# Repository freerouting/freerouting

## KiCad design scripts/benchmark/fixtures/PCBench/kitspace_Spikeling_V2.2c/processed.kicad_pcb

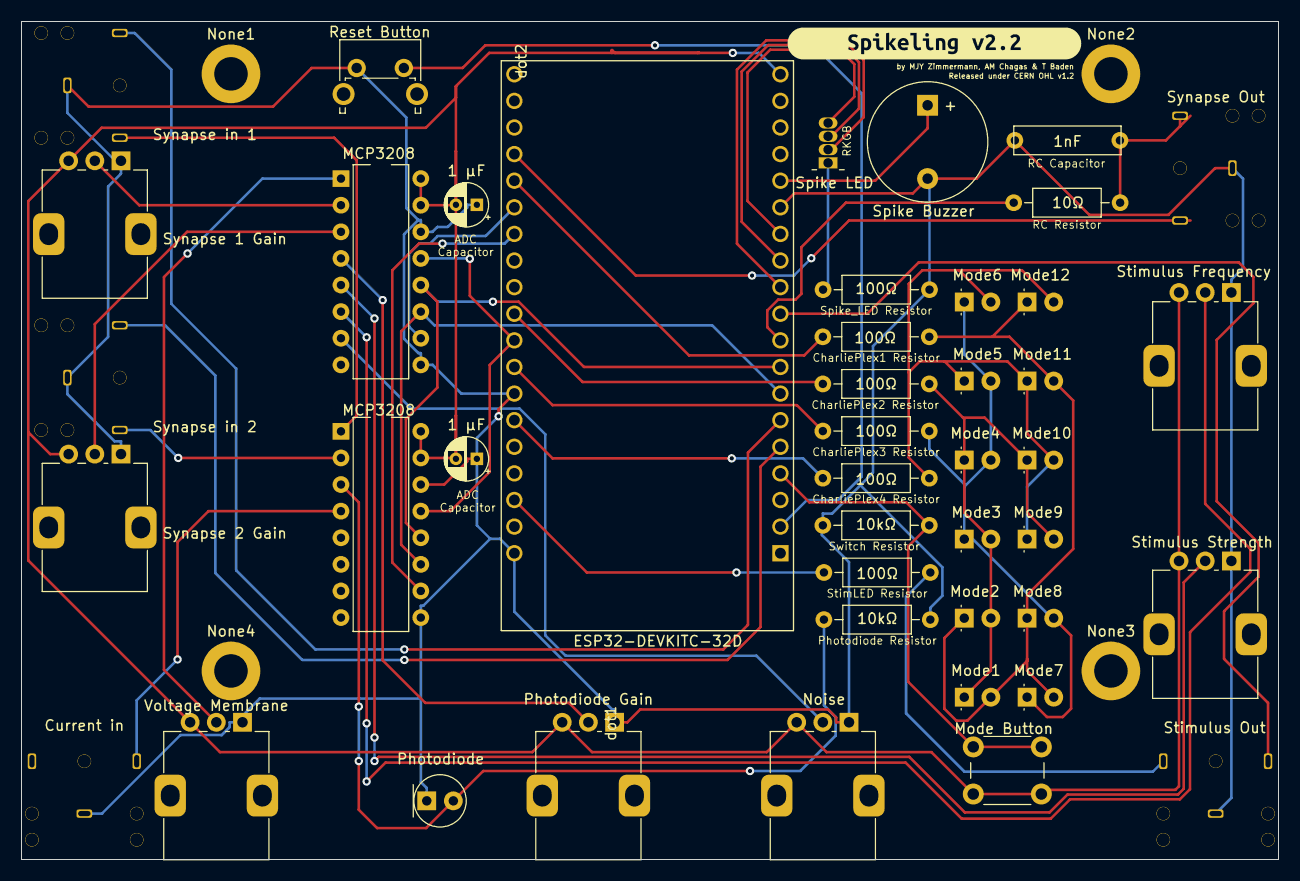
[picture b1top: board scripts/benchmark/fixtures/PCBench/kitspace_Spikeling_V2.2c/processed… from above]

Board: 2 copper layers, 120.0 x 80.0 mm, 51 parts (0 on the bottom side), 41 nets.

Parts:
BZ1: Spike Buzzer; Buzzer_11.5x9.5RM5
C1, C2: 1 μF; CP_Radial_D4.0mm_P2.00mm
C3: 1nF; C_Disc_D10.0mm_W2.5mm_P5.00mm
D1: Photodiode; LED_D5.0mm
D2: Mode1; LED_D3.0mm
D3: Mode2; LED_D3.0mm
D4: Mode3; LED_D3.0mm
D5: Mode4; LED_D3.0mm
D6: Mode5; LED_D3.0mm
D7: Mode6; LED_D3.0mm
D8: Mode7; LED_D3.0mm
D9: Mode8; LED_D3.0mm
D10: Mode9; LED_D3.0mm
D11: Mode10; LED_D3.0mm
D12: Mode11; LED_D3.0mm
D13: Mode12; LED_D3.0mm
D14: Spike LED; LED_D5.0mm-4_RGB
J1: Synapse Out; Spikeling Audio Jack 3.5mm
J2: Synapse in 1; Spikeling Audio Jack 3.5mm
J4: Current in; Spikeling Audio Jack 3.5mm
J5: Stimulus Out; Spikeling Audio Jack 3.5mm
None1, None3, None4: MountingHole_3.2mm_M3_DIN965_Pad
None2: MountingHole_M3; MountingHole_3.2mm_M3_DIN965_Pad
R1: 10Ω; R_Axial_DIN0207_L6.3mm_D2.5mm_P10.16mm_Horizontal
R2, R5: 10kΩ; R_Axial_DIN0207_L6.3mm_D2.5mm_P10.16mm_Horizontal
R3, R4, R6, R7, R8, R9: 100Ω; R_Axial_DIN0207_L6.3mm_D2.5mm_P10.16mm_Horizontal
RV1: Synapse 1 Gain; Spikeling Potentiometer
RV2: Synapse 2 Gain; Spikeling Potentiometer
RV3: Voltage Membrane; Spikeling Potentiometer
RV4: Noise; Spikeling Potentiometer
RV5: Photodiode Gain; Spikeling Potentiometer
RV6: Stimulus Strength; Spikeling Potentiometer
RV7: Stimulus Frequency; Spikeling Potentiometer
SW1: Mode Button; SW_PUSH_6mm_H13mm
SW2: Reset Button; Spikeling reset button
U1: ESP32-DEVKITC-32D; MODULE_ESP32-DEVKITC-32D
U2, U3: MCP3208; DIP-16_W7.62mm
dot1: Spikeling_neuron; Spikeling_Photoreceptor
dot2: Spikeling_neuron; Spikeling_Neuron
e: Synapse in 2; Spikeling Audio Jack 3.5mm
kibuzzard-633362FE: G***; kibuzzard-633362FE

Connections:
/00: U1.33, U2.10
/02: R6.1, U1.34
/04: U1.32, U3.10
/05: R7.1, U1.29
/12: D14.4, U1.13
/13: BZ1.1, U1.15
/14: D14.3, U1.12
/15: J1.T, U1.35
/18: U1.28, U2.13, U3.13
/19: R8.1, U1.27
/21: R9.1, U1.25
/22: R3.1, U1.22
/25: R1.1, U1.9
/26: J5.R, U1.10
/27: D14.1, U1.11
/32: U1.7, U2.11, U3.11
/33: U1.8, U2.12, U3.12
/34: U1.5, e.T
/35: J2.T, U1.6
/39: R5.1, SW1.1, U1.4
/100: RV3.2, U2.1
/101: RV1.2, U2.2
/102: RV2.2, U2.3
/103: RV5.2, U2.4
/104: RV6.2, U2.5
/105: RV7.2, U2.6
/106: RV4.2, U2.7
/200: J2.R, U3.1
/201: U3.2, e.R
/202: D1.2, R2.1, U3.3
/203: J4.R, U3.4
GNDREF: BZ1.2, C1.1, C2.1, C3.2, D1.1, J1.S, J2.S, J4.S, J5.S, R2.2, R4.1, R5.2, RV1.1, RV2.1, RV3.1, RV4.1, RV5.1, RV6.1, RV7.1, SW2.1, U1.14, U1.20, U1.26, U2.9, U2.14, U3.9, U3.14, e.S
unnamed: C3.1, J1.R, R1.2
unnamed: J5.T, R3.2
unnamed: D14.2, R4.2
unnamed: D2.2, D3.1, D8.2, D9.1, D12.2, D13.1, R6.2
unnamed: D2.1, D3.2, D4.2, D5.1, D10.2, D11.1, R7.2
unnamed: D4.1, D5.2, D6.2, D7.1, D8.1, D9.2, R8.2
unnamed: D6.1, D7.2, D10.1, D11.2, D12.1, D13.2, R9.2
unnamed: SW2.2, U1.2
VCC: C1.2, C2.2, RV1.3, RV2.3, RV3.3, RV4.3, RV5.3, RV6.3, RV7.3, SW1.2, U1.19, U2.15, U2.16, U3.15, U3.16

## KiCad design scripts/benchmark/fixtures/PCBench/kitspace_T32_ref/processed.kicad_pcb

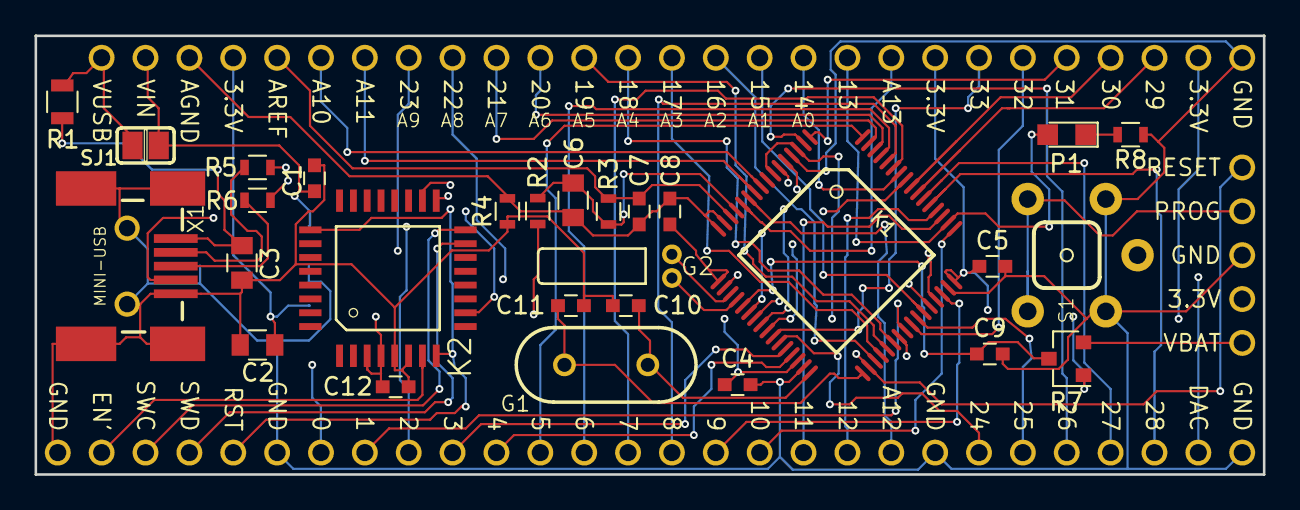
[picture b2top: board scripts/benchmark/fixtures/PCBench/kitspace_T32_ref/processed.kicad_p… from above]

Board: 4 copper layers, 71.1 x 25.4 mm, 89 parts (1 on the bottom side), 66 nets.

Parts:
C1, C4, C5, C7, C8, C9, C12: 0.1uF; C_0603
C2, C3, C6: 2.2uF; C_0805
C10, C11: 22pF; C_0603
G1: 16MHz; HC49US
G2: 32.768kHz; TC26H
K1: MK20DX256VLH7; LQFP64-05
K2: MKL04Z32VLC4; LQFP32-08
P1: LED_0805
R1: FUSE; R_0805
R2, R4: R_0603
R3, R8: 470R; R_0603
R5, R6: 33R; R_0603
R7: SOT-23
S1: ALPS_SKHH
SJ1: SOLDERJUMPER
SX1, SX2, SX3, SX4, SX5, SX6, SX7, SX8, SX9, SX10, SX11, SX12, SX13, SX14, SX15, SX16, SX17, SX18, SX19, SX20, SX21, SX22, SX23, SX24, SX25, SX26, SX27, SX28, SX29, SX30, SX31, SX32, SX33, SX34, SX35, SX36, SX37, SX38, SX39, SX40, SX41, SX42, SX43, SX44, SX45, SX46, SX47, SX48, SX49, SX50, SX51, SX52, SX53, SX54, SX55, SX56, SX57, SX58, SX59, SX60: PIN; PTH_39MIL
T1: MCP1825S; SOT-223
X1: MINI-USB; MOLEX_SD-67503-010

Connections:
/N$1: K2.7, SX59.1
/N$2: K1.22, K2.16, SX58.1
/N$3: K1.24, K2.17
/N$5: C10.1, G1.1, K1.32
/N$6: C11.1, G1.2, K1.33
/N$7: G2.2, K1.19
/N$8: G2.1, K1.20
/N$9: K2.18, S1.1, S1.2, SX40.1
/N$10: K1.5, R6.2
/N$11: C8.1, K1.17
/N$12: K1.34, K2.8, K2.25, SX38.1, SX56.1
/N$13: C7.1, K1.14, R3.2, SX16.1
/N$14: K1.6, R5.2
/N$15: C6.1, K1.13, R2.1, R3.1
/N$16: R6.1, X1.3
/N$17: R5.1, X1.2
/N$18: C3.1, R1.1, X1.1
/N$19: K1.23, K2.10, X1.4
/N$21: K1.45, SX5.1
/N$22: K1.44, SX6.1
/N$23: K1.63, SX7.1
/N$24: K1.62, SX8.1
/N$25: K1.37, SX9.1
/N$26: K1.38, SX10.1
/N$27: K1.36, SX11.1
/N$28: K1.35, SX13.1
/N$29: K1.43, SX15.1
/N$30: K1.58, SX17.1
/N$31: K1.50, P1.2, SX18.1
/N$32: K1.52, SX19.1
/N$33: K1.51, SX20.1
/N$34: K1.49, SX21.1
/N$35: K1.46, SX22.1
/N$36: K1.60, SX23.1
/N$37: K1.59, SX24.1
/N$38: K1.61, SX25.1
/N$39: K1.64, SX26.1
/N$40: K1.29, SX27.1
/N$41: K1.28, SX28.1
/N$42: K1.57, SX29.1
/N$43: K1.40, SX30.1
/N$44: K1.39, SX31.1
/N$45: K1.12, SX33.1
/N$46: K1.26, SX35.1
/N$47: K1.41, SX36.1
/N$48: K1.1, SX37.1
/N$49: K1.56, SX39.1
/N$50: K1.55, SX41.1
/N$51: K1.53, SX43.1
/N$52: P1.1, R8.2
/N$53: C6.2, C7.2, C8.2, K1.15, K1.16, R4.2, SX3.1
/N$54: K1.18, SX52.1
/N$55: K1.11, SX51.1
/N$57: K1.27, SX49.1
/N$58: K1.42, SX48.1
/N$59: K1.2, SX47.1
/N$60: K1.54, SX45.1
/N$61: C1.1, SJ1.2, SX2.1, T1.1
/N$63: R7.2, SX46.1
/N$64: K1.10, SX12.1
/N$65: K1.9, SX14.1
/N$67: R1.2, SJ1.1, SX1.1
/N$68: C9.1, K1.21, R7.3
/N$69: C2.1, C4.1, C5.1, C12.1, K1.3, K1.7, K1.30, K1.48, K2.3, K2.4, R2.2, R7.1, SX4.1, SX34.1, SX44.1, SX54.1, T1.3
/N$70: K1.25, K2.15, SX57.1
GND: C1.2, C2.2, C3.2, C4.2, C5.2, C9.2, C10.2, C11.2, C12.2, K1.4, K1.31, K1.47, K2.5, K2.6, R4.1, R8.1, S1.3, S1.4, SX32.1, SX42.1, SX50.1, SX53.1, SX55.1, SX60.1, T1.2, T1.4, X1.5, X1.P$1, X1.P$2, X1.P$3, X1.P$4, X1.P$5, X1.P$6

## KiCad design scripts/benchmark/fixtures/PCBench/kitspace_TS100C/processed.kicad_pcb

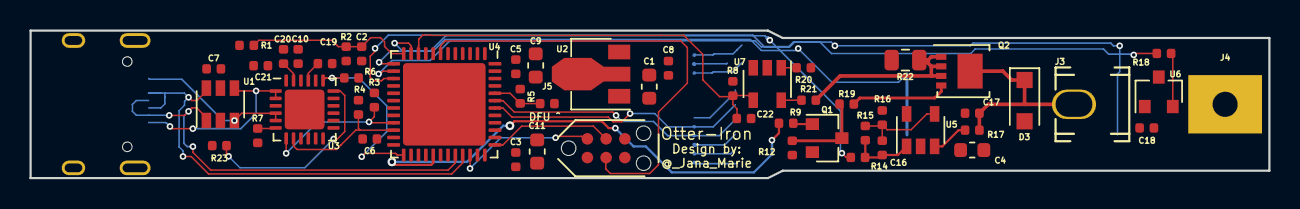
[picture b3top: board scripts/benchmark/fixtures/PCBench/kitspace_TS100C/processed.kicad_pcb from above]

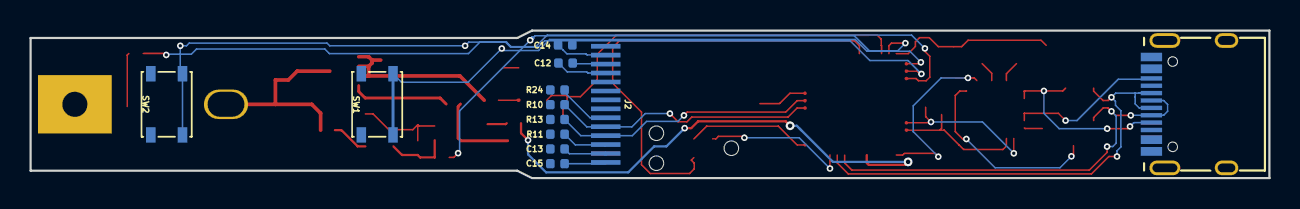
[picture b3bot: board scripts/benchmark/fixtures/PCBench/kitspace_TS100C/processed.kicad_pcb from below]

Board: 2 copper layers, 84.0 x 10.0 mm, 64 parts (12 on the bottom side), 42 nets.

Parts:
C1, C4, C9, C11: 1μF 25V; C_0603_1608Metric
C2, C3, C5, C6, C7, C8, C10, C18, C21, C22: 0.1μF; C_0402_1005Metric
C12, C13, C14, C15, C19, C20: 1μF 25V; C_0402_1005Metric
C16: 18p; C_0402_1005Metric
C17: DNP; C_0402_1005Metric
D3: B140-E3; D_SOD-123F
J1: USB_C_Receptacle_USB2.0; USB-C 16Pin
J2: OLED_64x32; 0.69OLED
J3: A; Keystone_3621
J4: B; 3622TR
J5: DNP; R_0402_1005Metric
P1: TC2030-CTX; TC2030-NL_SMALL
Q1: SS8050; SOT-23
Q2: DMP3017SFG; Diodes_PowerDI3333-8
R1, R11: 560k; R_0402_1005Metric
R2, R17: 100k; R_0402_1005Metric
R3, R4, R5, R6, R7, R8, R9, R10, R12, R13, R14, R16, R18, R23, R24: 2k37; R_0402_1005Metric
R15: 750k; R_0402_1005Metric
R19: 20; R_0402_1005Metric
R20, R21: 33; R_0402_1005Metric
R22: 10m; R_0805_2012Metric
SW1: key1; SW_SPST_PTS810
SW2: key2; SW_SPST_PTS810
U1: USBLC6-4SC6; SOT-23-6
U2: AP2204R-3.3; SOT-89-3
U3: STUSB4500QTR; QFN-24-1EP_4x4mm_P0.5mm_EP2.7x2.7mm
U4: STM32F072CBUx; QFN-48-1EP_7x7mm_P0.5mm_EP5.6x5.6mm
U5: OPA340NA; SOT-23-5
U6: MCP9700AT-ETT; SOT-23
U7: SI8540; SOT-23-5

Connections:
/OUT: C17.2, D3.1, J3.1, Q2.5, R17.1
CC1: J1.A5, U1.4, U3.1, U3.2
CC2: J1.B5, U1.3, U3.4, U3.5
IIN: C22.1, R8.1, U4.10, U7.4
INT_N: R6.1, U3.19, U4.25
unnamed: C12.1, J2.3
unnamed: C12.2, J2.4
unnamed: C13.1, J2.13
unnamed: C14.1, J2.2
unnamed: C15.1, J2.14
unnamed: C16.1, R15.1, R16.2, U5.4
unnamed: C16.2, R14.1, R15.2, U5.1
unnamed: C19.2, U3.21
unnamed: C20.1, U3.23
unnamed: J2.9, R24.1
unnamed: J2.12, R11.1
unnamed: J5.1, R5.2, U4.44
unnamed: Q1.1, R9.2
unnamed: Q1.3, R12.2, R19.1
unnamed: Q2.1, Q2.2, Q2.3, R21.2, R22.2
unnamed: Q2.4, R19.2
unnamed: R7.2, U3.6
unnamed: R17.2, U5.3
unnamed: R18.2, U6.2
unnamed: R20.2, U7.1
unnamed: R21.1, U7.5
unnamed: R23.1, U3.18
unnamed: SW1.2, U4.13
unnamed: SW2.2, U4.14
OLED_SCL: J2.10, R10.1, U4.42
OLED_SDA: J2.11, R13.1, U4.43
PWM: R9.1, U4.29
SCL: R3.1, U3.7, U4.21
SDA: R4.1, U3.8, U4.22
SWCLK: P1.4, U4.37
SWDIO: P1.2, U4.34
TREF: R18.1, U4.15
TTIP: R14.2, U4.11
UIN: C2.1, R1.2, R2.1, U4.12
USB_N: J1.A7, J1.B7, U1.1, U4.32
USB_P: J1.A6, J1.B6, U1.6, U4.33
nRST: P1.3, U4.7

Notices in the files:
scripts/benchmark/fixtures/PCBench/kitspace_Spikeling_V2.2c/processed.kicad_pcb:
This project is licensed under the GNU General Public License v3.0
The hardware is licensed under the CERN OHL v1.2
Released under CERN OHL v1.2
